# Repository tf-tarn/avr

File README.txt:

This is a collection of programs for the ATtiny412. They might run on
other AVR processors. They are to be regarded as proofs of concept, or
minimal working examples of specific functions. They are not to be
considered polished code.

adc/               reading the ADC
blink/             just blink an LED
oled/              small program that can display text and graphics on
                   an OLED display
pcb-devboard-412/  a small dev/breakout board for the ATtiny412,
                   implemented in kicad, with JLCPCB part numbers
                   for PCBA
pcb-devboard-416/  a pair of small dev/breakout boards for the ATtiny416,
                   implemented in kicad, with JLCPCB part numbers
                   for PCBA
pps/               an exercise in using timer interrupts
uart/              blocking IO with the UART
uart_interrupt/    non-blocking IO with the UART
common.mk          common makefile rules, included in makefiles in
                   subdirectories
README.txt         this file

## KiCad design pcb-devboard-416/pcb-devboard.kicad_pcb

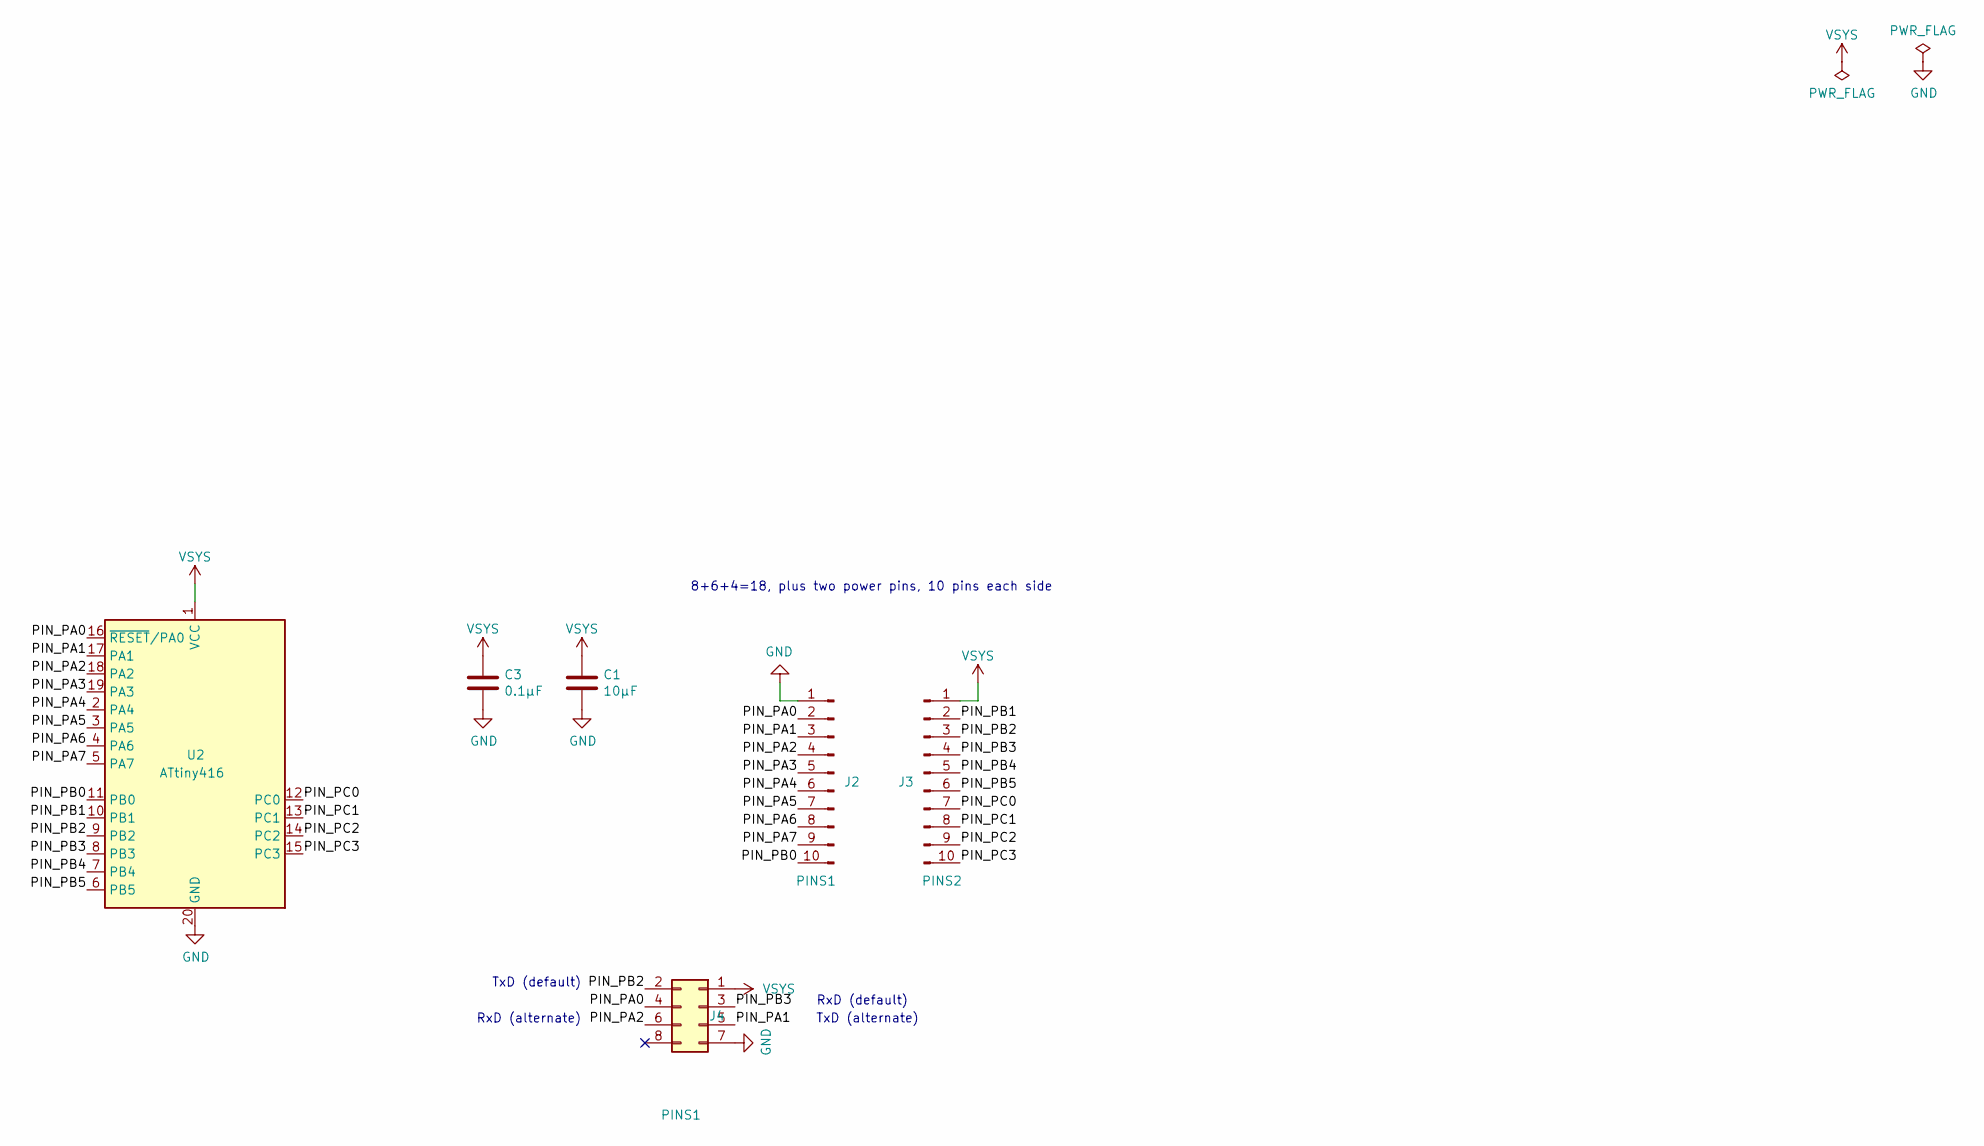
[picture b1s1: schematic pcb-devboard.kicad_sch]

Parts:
C1: 10μF; my_C_0805_2012Metric_Pad1.15x1.40mm_HandSolder; LCSC C14663
C3: 0.1μF; my_C_0805_2012Metric_Pad1.15x1.40mm_HandSolder; LCSC C14663
J2: PINS1; PinHeader_1x10_P2.54mm_Vertical
J3: PINS2; PinHeader_1x10_P2.54mm_Vertical
J4: PINS1; PinHeader_2x04_P2.54mm_Vertical
U2: ATtiny416; SOIC-20W_7.5x12.8mm_P1.27mm

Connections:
/PIN_PA0: J2.2, J4.4, U2.16 (~RESET/PA0)
/PIN_PA1: J2.3, J4.5, U2.17 (PA1)
/PIN_PA2: J2.4, J4.6, U2.18 (PA2)
/PIN_PA3: J2.5, U2.19 (PA3)
/PIN_PA4: J2.6, U2.2 (PA4)
/PIN_PA5: J2.7, U2.3 (PA5)
/PIN_PA6: J2.8, U2.4 (PA6)
/PIN_PA7: J2.9, U2.5 (PA7)
/PIN_PB0: J2.10, U2.11 (PB0)
/PIN_PB1: J3.2, U2.10 (PB1)
/PIN_PB2: J3.3, J4.2, U2.9 (PB2)
/PIN_PB3: J3.4, J4.3, U2.8 (PB3)
/PIN_PB4: J3.5, U2.7 (PB4)
/PIN_PB5: J3.6, U2.6 (PB5)
/PIN_PC0: J3.7, U2.12 (PC0)
/PIN_PC1: J3.8, U2.13 (PC1)
/PIN_PC2: J3.9, U2.14 (PC2)
/PIN_PC3: J3.10, U2.15 (PC3)
GND: C1.2, C3.2, J2.1, J4.7, U2.20 (GND)
VSYS: C1.1, C3.1, J3.1, J4.1, U2.1 (VCC)

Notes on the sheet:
TxD (alternate)
8+6+4=18, plus two power pins, 10 pins each side
RxD (default)
TxD (default)
RxD (alternate)

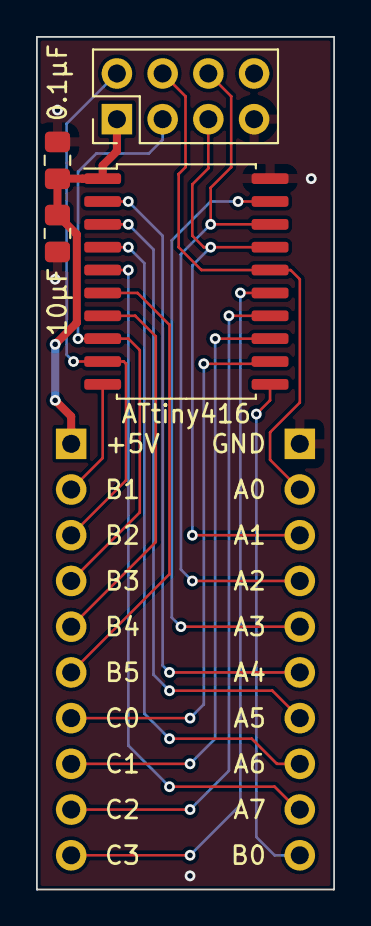
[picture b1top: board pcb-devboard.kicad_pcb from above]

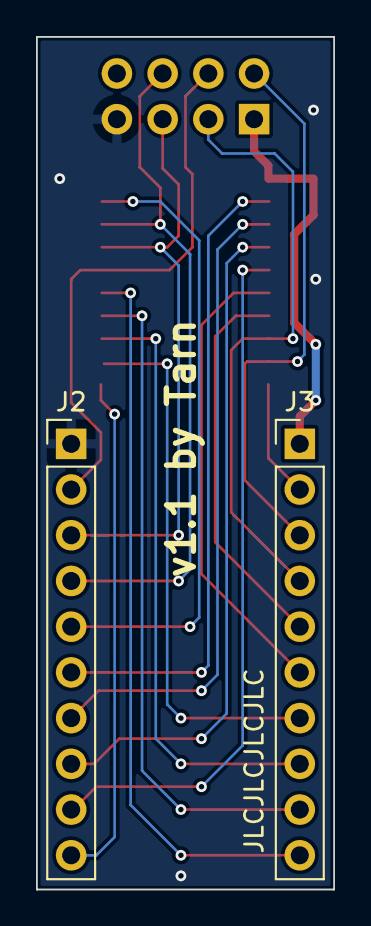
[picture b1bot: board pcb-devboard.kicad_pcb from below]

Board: 2 copper layers, 16.5 x 47.4 mm, 6 parts (2 on the bottom side), 20 nets.

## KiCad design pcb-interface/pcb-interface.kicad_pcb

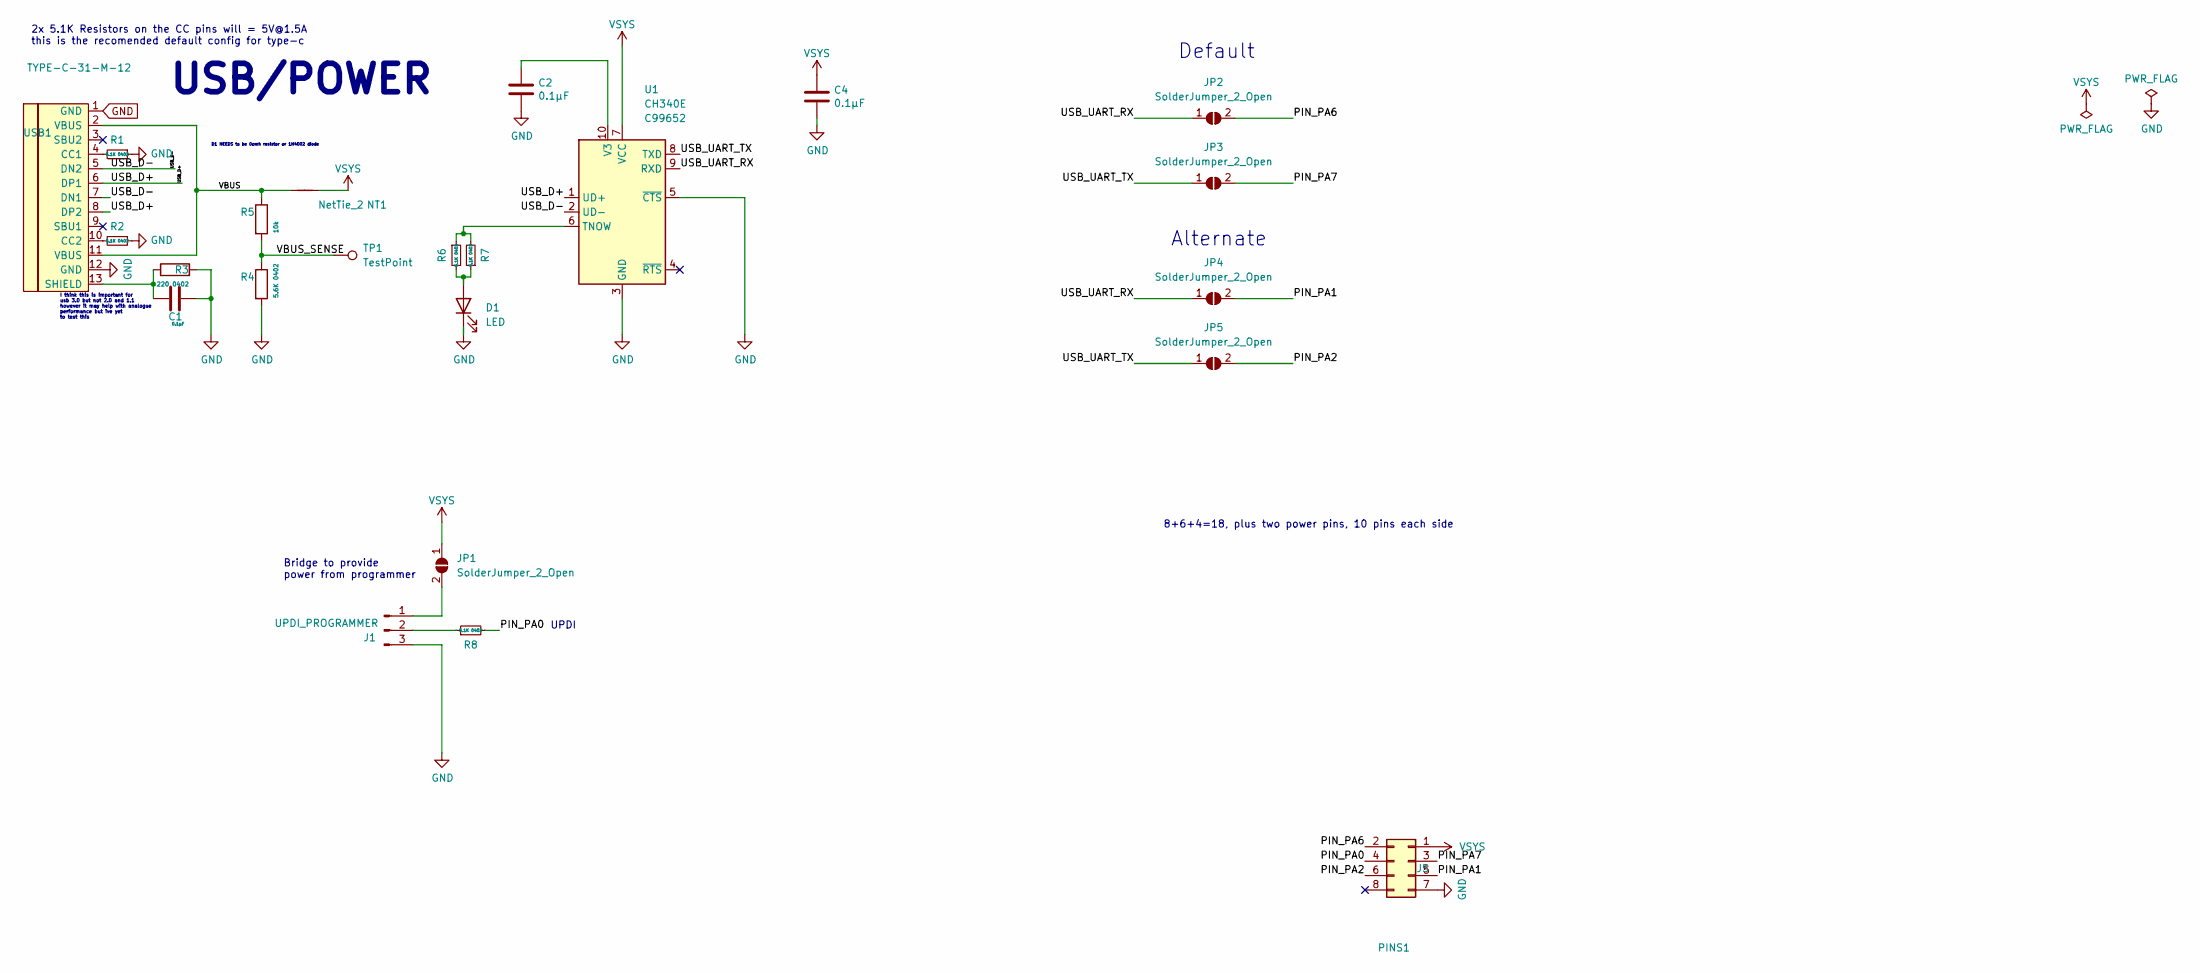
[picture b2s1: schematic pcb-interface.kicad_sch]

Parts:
C1, C2, C4: 0.1μF; C_0603_1608Metric; LCSC C14663
D1: LED; LED_0603_1608Metric; LCSC C2286
J1: UPDI_PROGRAMMER; PinHeader_1x03_P2.54mm_Vertical
J5: PINS1; PinSocket_2x04_P2.54mm_Vertical
JP1, JP2, JP3, JP4, JP5: SolderJumper_2_Open; SolderJumper-2_P1.3mm_Open_Pad1.0x1.5mm
NT1: NetTie_2; NetTie-2_SMD_Pad0.5mm
R1, R2, R6, R7, R8: 5.1K 0402; R_0402_1005Metric; LCSC C25905
R3: 220 0402; R_0402_1005Metric; LCSC C25091
R4: 5.6K 0402; R_0402_1005Metric; LCSC C25908
R5: 10k; R_0402_1005Metric; LCSC C25744
TP1: TestPoint; TestPoint_Pad_1.0x1.0mm
U1: CH340E; MSOP-10_3x3mm_P0.5mm; LCSC C99652
USB1: TYPE-C-31-M-12; HRO-TYPE-C-31-M-12; LCSC C165948

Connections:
/PIN_PA0: J5.4, R8.2
/PIN_PA1: J5.5, JP4.2 (B)
/PIN_PA2: J5.6, JP5.2 (B)
/PIN_PA6: J5.2, JP2.2 (B)
/PIN_PA7: J5.3, JP3.2 (B)
/USB_D+: U1.1 (UD+), USB1.6 (DP1), USB1.8 (DP2)
/USB_D-: U1.2 (UD-), USB1.5 (DN2), USB1.7 (DN1)
/USB_UART_RX: JP2.1 (A), JP4.1 (A), U1.9 (RXD)
/USB_UART_TX: JP3.1 (A), JP5.1 (A), U1.8 (TXD)
/VBUS: NT1.1, R5.1, USB1.2 (VBUS), USB1.11 (VBUS)
/VBUS_SENSE: R4.1, R5.2, TP1.1
GND: C1.1, C2.2, C4.2, D1.1 (K), J1.3, J5.7, R1.1, R2.1, R3.2, R4.2, U1.3 (GND), U1.5 (~CTS), USB1.1 (GND), USB1.12 (GND)
unnamed: C1.2, R3.1, USB1.13 (SHIELD)
unnamed: C2.1, U1.10 (V3)
unnamed: D1.2 (A), R6.2, R7.1
unnamed: J1.1, JP1.2 (B)
unnamed: J1.2, R8.1
unnamed: R1.2, USB1.4 (CC1)
unnamed: R2.2, USB1.10 (CC2)
unnamed: R6.1, R7.2, U1.6 (TNOW)
VSYS: C4.1, J5.1, JP1.1 (A), NT1.2, U1.7 (VCC)

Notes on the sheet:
2x 5.1K Resistors on the CC pins will = 5V@1.5A this is the recomended default config for type-c
Alternate
8+6+4=18, plus two power pins, 10 pins each side
Default
I think this is important for usb 3.0 but not 2.0 and 1.1 however it may help with analogue performance but ive yet to test this
UPDI
Bridge to provide power from programmer
D1 NEEDS to be 0omh resistor or 1N4002 diode
USB/POWER

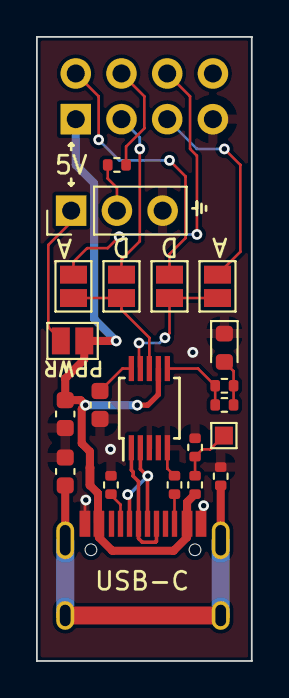
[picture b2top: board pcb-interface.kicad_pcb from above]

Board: 2 copper layers, 11.9 x 34.7 mm, 23 parts (1 on the bottom side), 21 nets.

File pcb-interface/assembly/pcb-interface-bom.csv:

Designator,Comment,Footprint,JLCPCB Part #
"C1, C2, C4, ",0.1μF,Capacitor_SMD:C_0603_1608Metric,C14663
"D1, ",LED,LED_SMD:LED_0603_1608Metric,C2286
"J1, ",UPDI_PROGRAMMER,Connector_PinHeader_2.54mm:PinHeader_1x03_P2.54mm_Vertical,
"J5, ",PINS1,Connector_PinSocket_2.54mm:PinSocket_2x04_P2.54mm_Vertical,
"JP1, JP2, JP3, JP4, JP5, ",SolderJumper_2_Open,Jumper:SolderJumper-2_P1.3mm_Open_Pad1.0x1.5mm,
"NT1, ",NetTie_2,NetTie:NetTie-2_SMD_Pad0.5mm,
"R1, R2, R6, R7, R8, ",5.1K 0402,Resistor_SMD:R_0402_1005Metric,C25905
"R3, ",220 0402,Resistor_SMD:R_0402_1005Metric,C25091
"R4, ",5.6K 0402,Resistor_SMD:R_0402_1005Metric,C25908
"R5, ",10k,Resistor_SMD:R_0402_1005Metric,C25744
"TP1, ",TestPoint,mine:TestPoint_Pad_1.0x1.0mm,
"U1, ",CH340E,Package_SO:MSOP-10_3x3mm_P0.5mm,C99652
"USB1, ",TYPE-C-31-M-12,HRO:HRO-TYPE-C-31-M-12,C165948

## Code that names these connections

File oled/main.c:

#include <avr/interrupt.h>
#include <avr/io.h>
#include <util/delay.h>

#include "uart.h"
#include "oled.h"
#include "terminal.h"

#define RXBUFLEN (1 << 4)
#define RXBUFLEN_MASK (RXBUFLEN - 1)

volatile char rxbuf[RXBUFLEN];
volatile unsigned char rxbuf_start = 0;
volatile unsigned char rxbuf_end = 0;


enum {
    M_TEXT,
    M_GFX
};

struct {
    uint8_t row;
    uint8_t col;
} gfx;

static void set_row(uint8_t r) {
    oled_command(0x22); // set page address
    oled_command(r);
    oled_command(r);
}
static void return_carriage() {
    oled_command(0x21); // set column address
    oled_command(0);
    oled_command(SCREENWIDTH - 1);
}

void gfx_begin() {
    gfx.row = 0;
    gfx.col = 0;
    set_row(0);
    return_carriage();
}

char gfx_draw(uint8_t c) {
    if (gfx.col > SCREENWIDTH - 1) {
        gfx.col = 1;
        ++gfx.row;
        if (gfx.row >= SCREENHEIGHT / 8) {
            // graphics drawing has finished
            return 1;
        }
        set_row(gfx.row);
        return_carriage();
    } else {
        ++gfx.col;
    }

    oled_data(c);

    return 0;
}

int main (void)
{
    char mode = M_GFX;

    cli();

    // Use alternate pins (TX on PA1, RX on PA2)
    // Use alternate pins (SCK on PA3, MOSI on PA6)
    PORTMUX_CTRLB = PORTMUX_SPI0_ALTERNATE_gc | PORTMUX_USART0_ALTERNATE_gc;

    PORTA.DIRSET =
        (1 << 0) // reset
        | (1 << 7) // data/command
        | (1 << 6) | (1 << 3) // SPI
        | (1 << 1); // UART

    uart_init();

    _delay_ms(100);
    PORTA.OUTCLR = (1 << 0);
    _delay_ms(100);
    PORTA.OUTSET = (1 << 0);

    oled_init();
    term_clear();
    sei();

    _delay_ms(100);
    term_write_s("Hello\r\nReady to receive\r\ngraphics data.");
    gfx_begin();

    unsigned char c = 'U';
    while (1) {

        /* cli(); */
        USART0.CTRLA &= ~USART_RXCIE_bm;
        if (rxbuf_start == rxbuf_end) {
            USART0.CTRLA |= USART_RXCIE_bm;
            continue;
        }
        c = rxbuf[rxbuf_start];
        rxbuf_start = (rxbuf_start + 1u) & RXBUFLEN_MASK;
        /* sei(); */
        USART0.CTRLA |= USART_RXCIE_bm;

        if (mode == M_TEXT) {
            switch (c) {
            case 0x3:
                term_clear();
                break;
            case 0x4:
                mode = M_GFX;
                gfx_begin();
                break;
            default:
                term_write(c);
            }
        } else if (mode == M_GFX) {
            if (gfx_draw(c)) {
                mode = M_TEXT;
            }
        }
        _delay_us(300);
    }
    return 0;

}

ISR(USART0_RXC_vect) {
    /* if ((((rxbuf_end + RXBUFLEN) - rxbuf_start) & RXBUFLEN_MASK) < (RXBUFLEN - 2)) { */
    /*     // drop a byte.. oops. */
    /*     return; */
    /* } */
    rxbuf[rxbuf_end] = USART0.RXDATAL;
    rxbuf_end = (rxbuf_end + 1u) & RXBUFLEN_MASK;
}

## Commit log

2023-10-26 blink
2023-10-26 Add UART test program
2023-10-27 Clean up makefiles
2023-10-27 temp
2023-10-27 Add dev board schematic draft
2023-10-27 Schematic improvements and first layout draft
2023-10-28 Layout improvements
2023-10-28 Version 1 as manufactured by JLCPCB
2023-11-11 PPS draft
2023-11-11 Make variable set in interrupt volatile
2023-11-11 Clean up whitespace
2023-11-11 Add PPS monitoring program; update gitignore
2023-11-11 Clean up; reply to PPS message
2023-11-11 Add ADC test program
2023-11-11 Use watchdog
2023-11-11 Create async UART implementation
2023-11-11 Make UART transmission work asynchronously
2023-11-11 Add README
2023-11-11 Port OLED code from PIC; add Makefile common include
2023-11-13 OLED graphics; improve common.mk
2023-11-13 Improve things; make the program more capable
2023-11-14 Don't use unsigned
2024-03-05 Add first version of dev board for ATtiny416
2024-03-05 Rename pcb-devboard to pcb-devboard-412
2024-04-18 Add pcb-interface
2024-04-18 416 dev board: Version 1.0 as manufactured
2024-04-18 41x interface board: Version 1.0 as manufactured
2024-05-12 41x interface board: Version 1.1 as manufactured
